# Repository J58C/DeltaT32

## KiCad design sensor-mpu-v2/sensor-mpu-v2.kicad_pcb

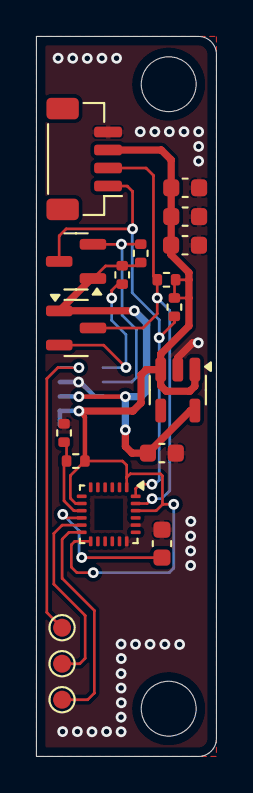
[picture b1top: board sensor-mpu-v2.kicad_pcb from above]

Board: 2 copper layers, 10.0 x 40.0 mm, 20 parts (1 on the bottom side), 12 nets.

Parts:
C1: 1uF 16V; C_0603_1608Metric
C2: 10nF 16V; C_0603_1608Metric
C3: 2.2uF 16V; C_0603_1608Metric
C4, C5: 100nF 16V; C_0603_1608Metric
J1: JST SH1.0; JST_SH_BM04B-SRSS-TB_1x04-1MP_P1.00mm_Vertical
Q1, Q2: BSS138; SOT-23
R1: 0R; R_0402_1005Metric
R2, R3, R4, R5, R6: 10K; R_0402_1005Metric
TP1: MPU_FSYNC; TestPoint_Pad_D1.0mm
TP2: MPU_INT; TestPoint_Pad_D1.0mm
TP3: MAX_INT; TestPoint_Pad_D1.0mm
U1: LN1134A182MR-G; SOT-23-5
U2: MPU-9250; InvenSense_QFN-24_3x3mm_P0.4mm_NoMask
U3: MAX30102; Maxim_OLGA-14_3.3x5.6mm_P0.8mm

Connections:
+1V8: C3.1, Q1.1 (G), Q2.1 (G), R3.1, R4.1, U1.5 (VOUT), U3.11 (VDD)
GND: C1.2, C2.2, C3.2, C4.2, C5.2, J1.4, R2.2, U1.2 (GND), U2.18 (GND), U2.20 (RESV_GND), U3.4 (PGND), U3.12 (GND)
unnamed: R1.2, R2.1, U2.9 (AD0/MISO)
unnamed: TP1.1, U2.11 (FSYNC)
unnamed: TP2.1, U2.12 (INT)
unnamed: C5.1, U2.10 (REGOUT)
unnamed: TP3.1, U3.13 (~INT)
SCL: J1.2, Q1.3 (D), R6.1, U2.23 (SCL/SCLK)
SCL_1V8: Q1.2 (S), R4.2, U3.2 (SCL)
SDA: J1.1, Q2.3 (D), R5.1, U2.24 (SDA/MOSI)
SDA_1V8: Q2.2 (S), R3.2, U3.3 (SDA)
VDDIO: C1.1, C2.1, C4.1, J1.3, R1.1, R5.2, R6.2, U1.1 (VIN), U1.3 (EN), U2.1 (RESV_VDDIO), U2.8 (VDDIO), U2.13 (VDD), U2.22 (~CS), U3.9 (VLED+), U3.10 (VLED+)
